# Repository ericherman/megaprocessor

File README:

http://www.megaprocessor.com/
(C) 2014-2016 James Newman.

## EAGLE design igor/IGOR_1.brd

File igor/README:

IGOR

This consists of an FPGA development board from Lattice piggybacking on
a board that provides 3 to 5V level translation to allow it to talk to
the Megaprocessor. I was originally only going to build one of these but
I ended up splitting out its functions (control, memory, peripherals) to
try and make it easier to see what was happening rather than just having
one board doing magic.
He's described in more detail here.
http://www.megaprocessor.com/igor.html

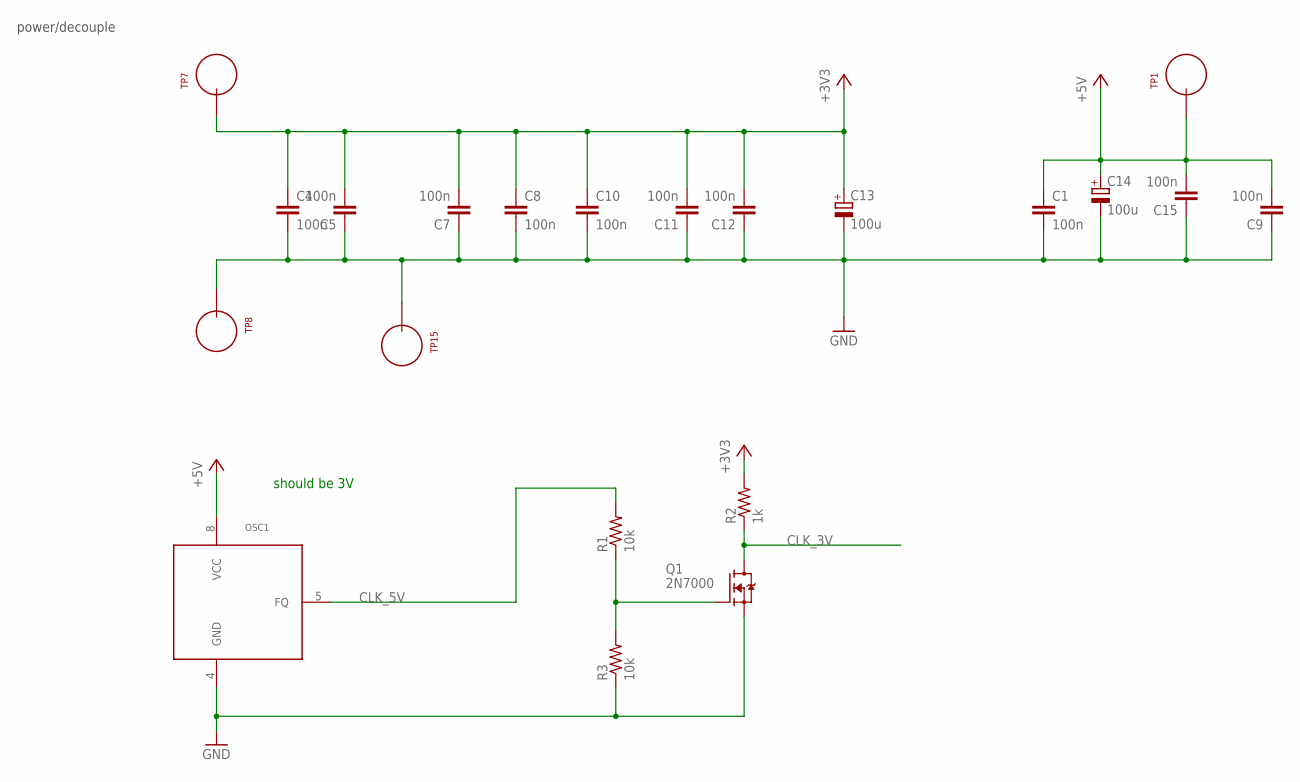
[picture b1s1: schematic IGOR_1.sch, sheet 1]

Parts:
C1, C4, C5, C7, C8, C9, C10, C11, C12, C15: 100n; CAP_P2INCH
C13, C14: 100u; POLARISED_CAP_2P5_6P3MM
OSC1: OSC_12P9_MM
Q1: 2N7000; TO92-DGS
R1, R3: 10k; R_P2INCH
R2: 1k; R_P2INCH
TP1, TP7, TP8, TP15: TEST_LOOP

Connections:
+3V3: C4.1, C5.2, C7.2, C8.1, C10.1, C11.2, C12.2, C13.A, R2.2, TP7.P$1; also elsewhere on the board
+5V: C1.1, C9.2, C14.A, C15.2, OSC1.8 (VCC), TP1.P$1; also elsewhere on the board
CLK_3V: Q1.D, R2.1; also elsewhere on the board
CLK_5V: Q1.G, R1.1, R3.2
GND: C1.2, C4.2, C5.1, C7.1, C8.2, C9.1, C10.2, C11.1, C12.1, C13.K, C14.K, C15.1, OSC1.4 (GND), Q1.S, R3.1, TP8.P$1, TP15.P$1; also elsewhere on the board
unnamed: OSC1.5 (FQ), R1.2

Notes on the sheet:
power/decouple
should be 3V

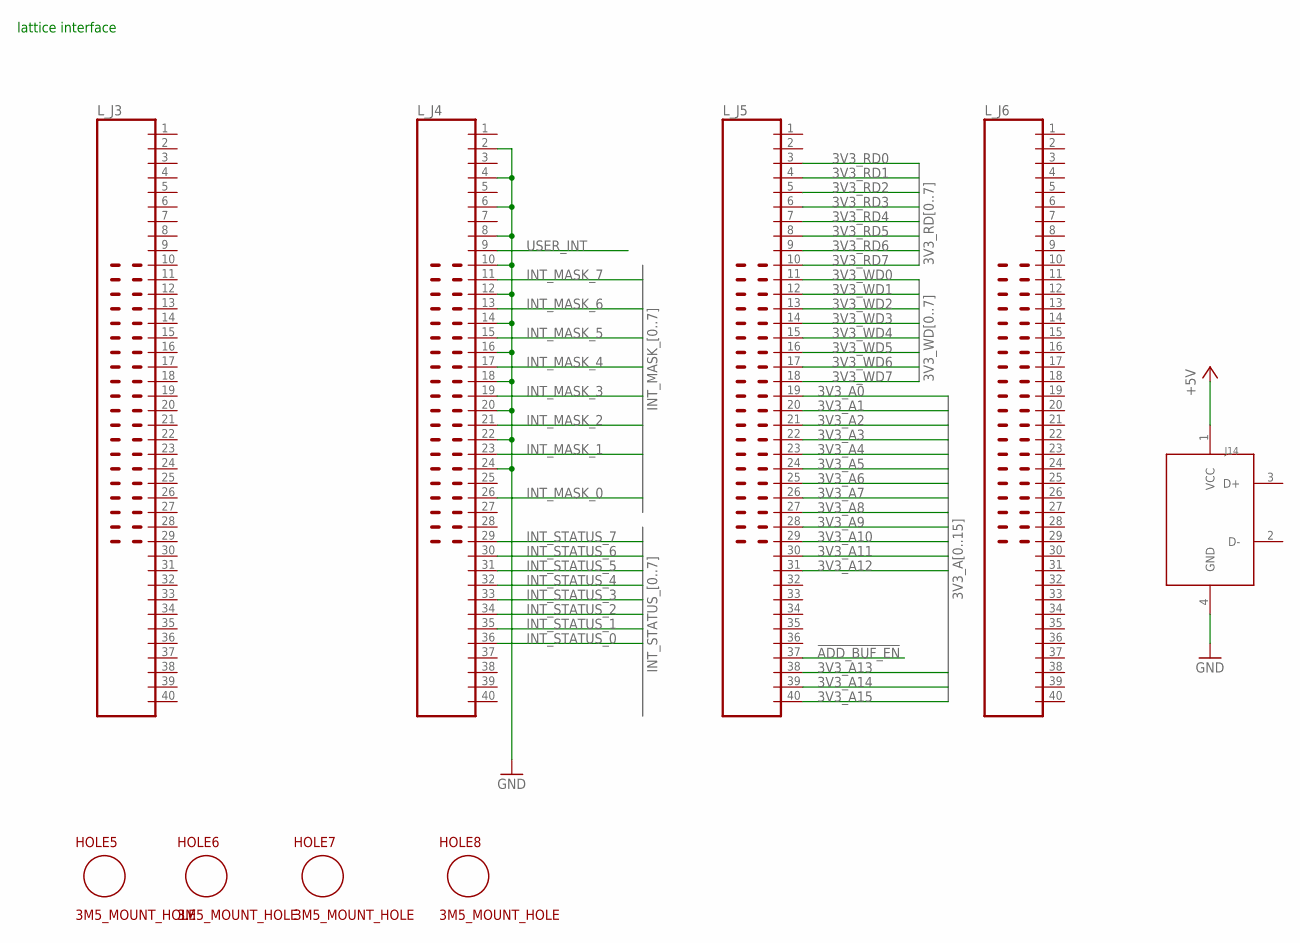
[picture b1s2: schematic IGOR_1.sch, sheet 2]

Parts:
HOLE5, HOLE6, HOLE7, HOLE8: 3M5_MOUNT_HOLE; 3P5M_HOLE
J14: USB_TYPE_A
L_J3, L_J4, L_J5, L_J6: JUMP_20X2

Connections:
3V3_A0: L_J5.19; also elsewhere on the board
3V3_A1: L_J5.20; also elsewhere on the board
3V3_A2: L_J5.21; also elsewhere on the board
3V3_A3: L_J5.22; also elsewhere on the board
3V3_A4: L_J5.23; also elsewhere on the board
3V3_A5: L_J5.24; also elsewhere on the board
3V3_A6: L_J5.25; also elsewhere on the board
3V3_A7: L_J5.26; also elsewhere on the board
3V3_A8: L_J5.27; also elsewhere on the board
3V3_A9: L_J5.28; also elsewhere on the board
3V3_A10: L_J5.29; also elsewhere on the board
3V3_A11: L_J5.30; also elsewhere on the board
3V3_A12: L_J5.31; also elsewhere on the board
3V3_A13: L_J5.38; also elsewhere on the board
3V3_A14: L_J5.39; also elsewhere on the board
3V3_A15: L_J5.40; also elsewhere on the board
3V3_RD0: L_J5.3; also elsewhere on the board
3V3_RD1: L_J5.4; also elsewhere on the board
3V3_RD2: L_J5.5; also elsewhere on the board
3V3_RD3: L_J5.6; also elsewhere on the board
3V3_RD4: L_J5.7; also elsewhere on the board
3V3_RD5: L_J5.8; also elsewhere on the board
3V3_RD6: L_J5.9; also elsewhere on the board
3V3_RD7: L_J5.10; also elsewhere on the board
3V3_WD0: L_J5.11; also elsewhere on the board
3V3_WD1: L_J5.12; also elsewhere on the board
3V3_WD2: L_J5.13; also elsewhere on the board
3V3_WD3: L_J5.14; also elsewhere on the board
3V3_WD4: L_J5.15; also elsewhere on the board
3V3_WD5: L_J5.16; also elsewhere on the board
3V3_WD6: L_J5.17; also elsewhere on the board
3V3_WD7: L_J5.18; also elsewhere on the board
!ADD_BUF_EN: L_J5.37; also elsewhere on the board
+5V: J14.1 (VCC); also elsewhere on the board
GND: J14.4 (GND), L_J4.2, L_J4.4, L_J4.6, L_J4.8, L_J4.10, L_J4.12, L_J4.14, L_J4.16, L_J4.18, L_J4.20, L_J4.22, L_J4.24; also elsewhere on the board
INT_MASK_0: L_J4.26; also elsewhere on the board
INT_MASK_1: L_J4.23; also elsewhere on the board
INT_MASK_2: L_J4.21; also elsewhere on the board
INT_MASK_3: L_J4.19; also elsewhere on the board
INT_MASK_4: L_J4.17; also elsewhere on the board
INT_MASK_5: L_J4.15; also elsewhere on the board
INT_MASK_6: L_J4.13; also elsewhere on the board
INT_MASK_7: L_J4.11; also elsewhere on the board
INT_STATUS_0: L_J4.36; also elsewhere on the board
INT_STATUS_1: L_J4.35; also elsewhere on the board
INT_STATUS_2: L_J4.34; also elsewhere on the board
INT_STATUS_3: L_J4.33; also elsewhere on the board
INT_STATUS_4: L_J4.32; also elsewhere on the board
INT_STATUS_5: L_J4.31; also elsewhere on the board
INT_STATUS_6: L_J4.30; also elsewhere on the board
INT_STATUS_7: L_J4.29; also elsewhere on the board
USER_INT: L_J4.9; also elsewhere on the board

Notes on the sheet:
lattice interface

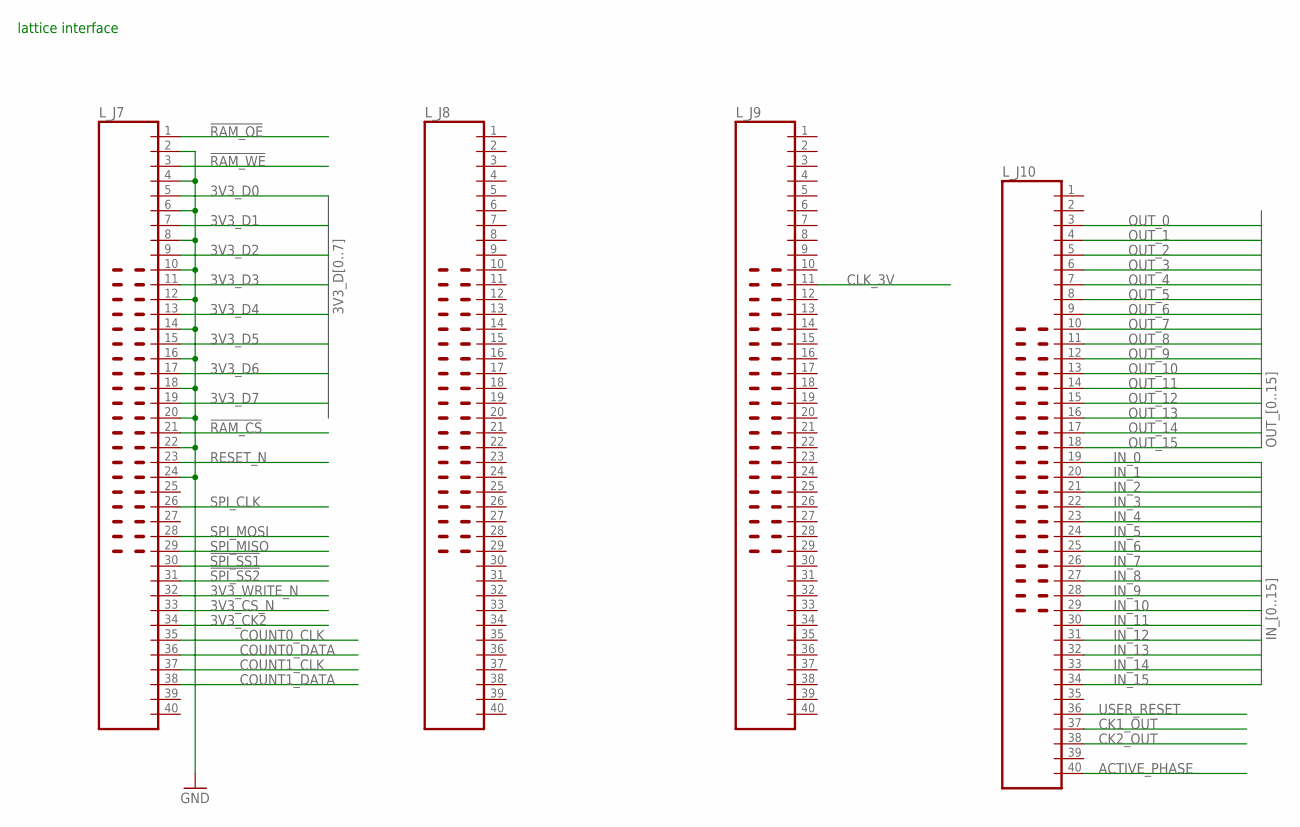
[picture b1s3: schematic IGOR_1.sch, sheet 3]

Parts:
L_J7, L_J8, L_J9, L_J10: JUMP_20X2

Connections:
3V3_CK2: L_J7.34; also elsewhere on the board
3V3_CS_N: L_J7.33; also elsewhere on the board
3V3_D0: L_J7.5; also elsewhere on the board
3V3_D1: L_J7.7; also elsewhere on the board
3V3_D2: L_J7.9; also elsewhere on the board
3V3_D3: L_J7.11; also elsewhere on the board
3V3_D4: L_J7.13; also elsewhere on the board
3V3_D5: L_J7.15; also elsewhere on the board
3V3_D6: L_J7.17; also elsewhere on the board
3V3_D7: L_J7.19; also elsewhere on the board
3V3_WRITE_N: L_J7.32; also elsewhere on the board
!RAM_CS: L_J7.21; also elsewhere on the board
!RAM_OE: L_J7.1; also elsewhere on the board
!RAM_WE: L_J7.3; also elsewhere on the board
!SPI_SS1: L_J7.30; also elsewhere on the board
!SPI_SS2: L_J7.31; also elsewhere on the board
ACTIVE_PHASE: L_J10.40; also elsewhere on the board
CK1_OUT: L_J10.37; also elsewhere on the board
CK2_OUT: L_J10.38; also elsewhere on the board
CLK_3V: L_J9.11; also elsewhere on the board
COUNT0_CLK: L_J7.35; also elsewhere on the board
COUNT0_DATA: L_J7.36; also elsewhere on the board
COUNT1_CLK: L_J7.37; also elsewhere on the board
COUNT1_DATA: L_J7.38; also elsewhere on the board
GND: L_J7.2, L_J7.4, L_J7.6, L_J7.8, L_J7.10, L_J7.12, L_J7.14, L_J7.16, L_J7.18, L_J7.20, L_J7.22, L_J7.24; also elsewhere on the board
IN_0: L_J10.19; also elsewhere on the board
IN_1: L_J10.20; also elsewhere on the board
IN_2: L_J10.21; also elsewhere on the board
IN_3: L_J10.22; also elsewhere on the board
IN_4: L_J10.23; also elsewhere on the board
IN_5: L_J10.24; also elsewhere on the board
IN_6: L_J10.25; also elsewhere on the board
IN_7: L_J10.26; also elsewhere on the board
IN_8: L_J10.27; also elsewhere on the board
IN_9: L_J10.28; also elsewhere on the board
IN_10: L_J10.29; also elsewhere on the board
IN_11: L_J10.30; also elsewhere on the board
IN_12: L_J10.31; also elsewhere on the board
IN_13: L_J10.32; also elsewhere on the board
IN_14: L_J10.33; also elsewhere on the board
IN_15: L_J10.34; also elsewhere on the board
OUT_0: L_J10.3; also elsewhere on the board
OUT_1: L_J10.4; also elsewhere on the board
OUT_2: L_J10.5; also elsewhere on the board
OUT_3: L_J10.6; also elsewhere on the board
OUT_4: L_J10.7; also elsewhere on the board
OUT_5: L_J10.8; also elsewhere on the board
OUT_6: L_J10.9; also elsewhere on the board
OUT_7: L_J10.10; also elsewhere on the board
OUT_8: L_J10.11; also elsewhere on the board
OUT_9: L_J10.12; also elsewhere on the board
OUT_10: L_J10.13; also elsewhere on the board
OUT_11: L_J10.14; also elsewhere on the board
OUT_12: L_J10.15; also elsewhere on the board
OUT_13: L_J10.16; also elsewhere on the board
OUT_14: L_J10.17; also elsewhere on the board
OUT_15: L_J10.18; also elsewhere on the board
RESET_N: L_J7.23; also elsewhere on the board
SPI_CLK: L_J7.26; also elsewhere on the board
SPI_MISO: L_J7.29; also elsewhere on the board
SPI_MOSI: L_J7.28; also elsewhere on the board
USER_RESET: L_J10.36; also elsewhere on the board

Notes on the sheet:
lattice interface

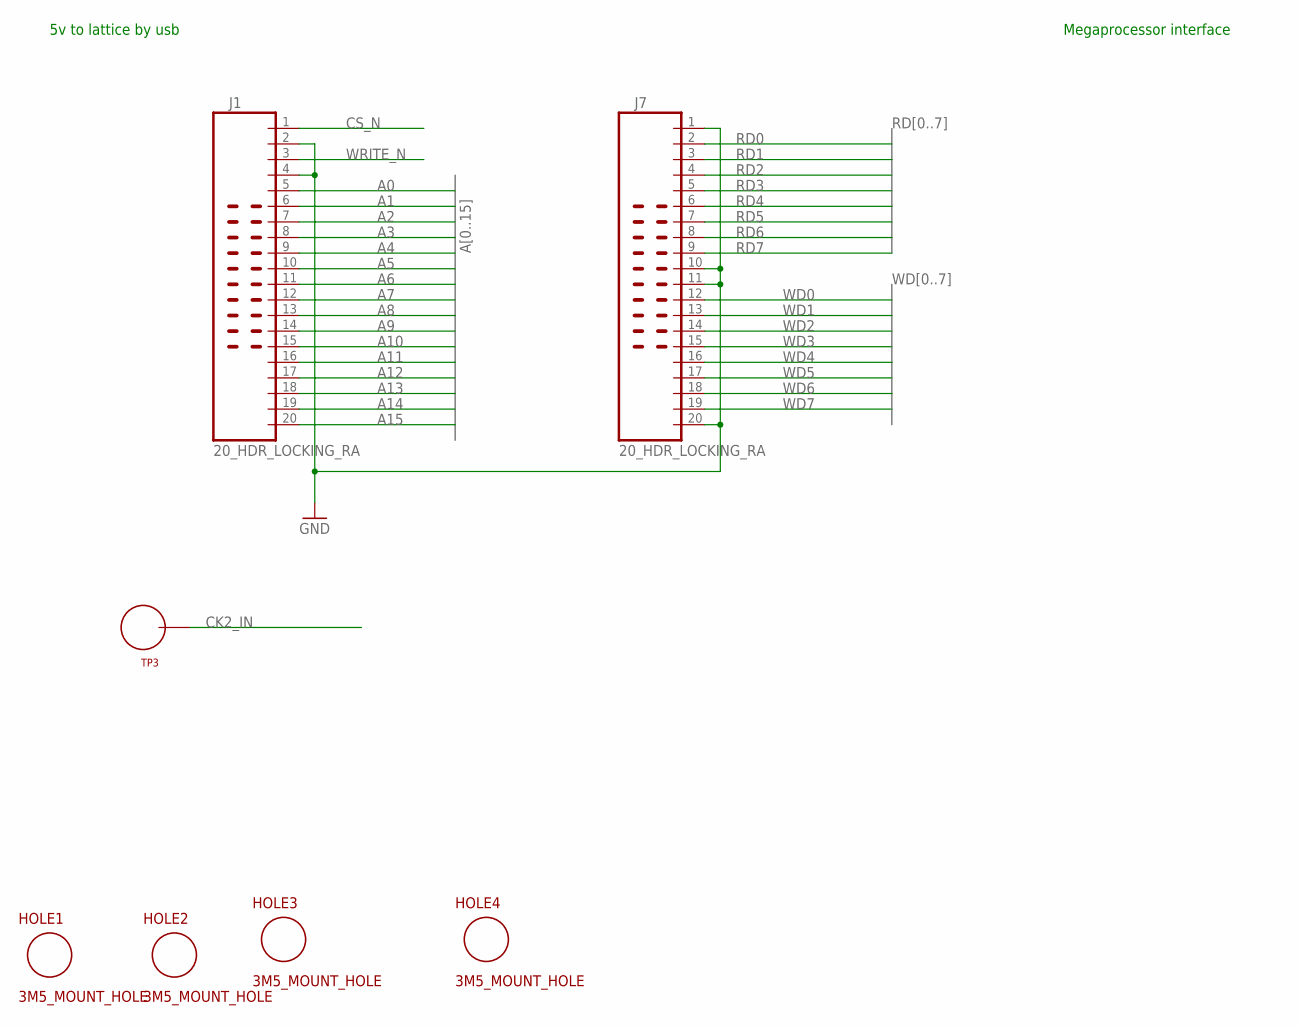
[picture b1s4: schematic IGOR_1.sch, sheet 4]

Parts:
HOLE1, HOLE2, HOLE3, HOLE4: 3M5_MOUNT_HOLE; 3P5M_HOLE
J1, J7: 20_HDR_LOCKING_RA
TP3: TEST_LOOP

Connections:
A0: J1.5; also elsewhere on the board
A1: J1.6; also elsewhere on the board
A2: J1.7; also elsewhere on the board
A3: J1.8; also elsewhere on the board
A4: J1.9; also elsewhere on the board
A5: J1.10; also elsewhere on the board
A6: J1.11; also elsewhere on the board
A7: J1.12; also elsewhere on the board
A8: J1.13; also elsewhere on the board
A9: J1.14; also elsewhere on the board
A10: J1.15; also elsewhere on the board
A11: J1.16; also elsewhere on the board
A12: J1.17; also elsewhere on the board
A13: J1.18; also elsewhere on the board
A14: J1.19; also elsewhere on the board
A15: J1.20; also elsewhere on the board
CK2_IN: TP3.P$1; also elsewhere on the board
CS_N: J1.1; also elsewhere on the board
GND: J1.2, J1.4, J7.1, J7.10, J7.11, J7.20; also elsewhere on the board
RD0: J7.2; also elsewhere on the board
RD1: J7.3; also elsewhere on the board
RD2: J7.4; also elsewhere on the board
RD3: J7.5; also elsewhere on the board
RD4: J7.6; also elsewhere on the board
RD5: J7.7; also elsewhere on the board
RD6: J7.8; also elsewhere on the board
RD7: J7.9; also elsewhere on the board
WD0: J7.12; also elsewhere on the board
WD1: J7.13; also elsewhere on the board
WD2: J7.14; also elsewhere on the board
WD3: J7.15; also elsewhere on the board
WD4: J7.16; also elsewhere on the board
WD5: J7.17; also elsewhere on the board
WD6: J7.18; also elsewhere on the board
WD7: J7.19; also elsewhere on the board
WRITE_N: J1.3; also elsewhere on the board

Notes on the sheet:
5v to lattice by usb
Megaprocessor interface

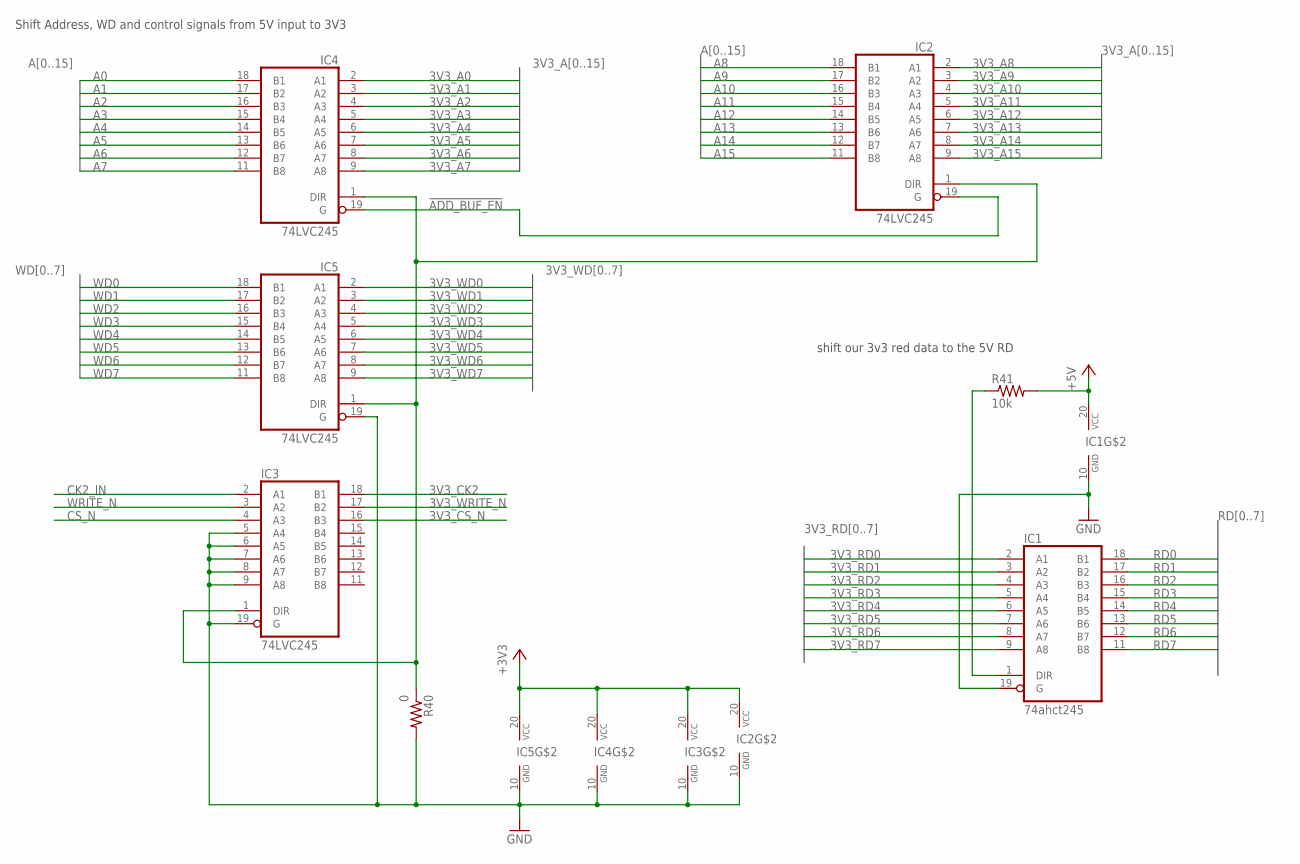
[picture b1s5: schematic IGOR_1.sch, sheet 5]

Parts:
IC1: 74ahct245; DIP20
IC2, IC3, IC4, IC5: 74LVC245; DIP20
R40: 0; R_P2INCH
R41: 10k; R_P2INCH

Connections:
3V3_A0: IC4.2 (A1); also elsewhere on the board
3V3_A1: IC4.3 (A2); also elsewhere on the board
3V3_A2: IC4.4 (A3); also elsewhere on the board
3V3_A3: IC4.5 (A4); also elsewhere on the board
3V3_A4: IC4.6 (A5); also elsewhere on the board
3V3_A5: IC4.7 (A6); also elsewhere on the board
3V3_A6: IC4.8 (A7); also elsewhere on the board
3V3_A7: IC4.9 (A8); also elsewhere on the board
3V3_A8: IC2.2 (A1); also elsewhere on the board
3V3_A9: IC2.3 (A2); also elsewhere on the board
3V3_A10: IC2.4 (A3); also elsewhere on the board
3V3_A11: IC2.5 (A4); also elsewhere on the board
3V3_A12: IC2.6 (A5); also elsewhere on the board
3V3_A13: IC2.7 (A6); also elsewhere on the board
3V3_A14: IC2.8 (A7); also elsewhere on the board
3V3_A15: IC2.9 (A8); also elsewhere on the board
3V3_CK2: IC3.18 (B1); also elsewhere on the board
3V3_CS_N: IC3.16 (B3); also elsewhere on the board
3V3_RD0: IC1.2 (A1); also elsewhere on the board
3V3_RD1: IC1.3 (A2); also elsewhere on the board
3V3_RD2: IC1.4 (A3); also elsewhere on the board
3V3_RD3: IC1.5 (A4); also elsewhere on the board
3V3_RD4: IC1.6 (A5); also elsewhere on the board
3V3_RD5: IC1.7 (A6); also elsewhere on the board
3V3_RD6: IC1.8 (A7); also elsewhere on the board
3V3_RD7: IC1.9 (A8); also elsewhere on the board
3V3_WD0: IC5.2 (A1); also elsewhere on the board
3V3_WD1: IC5.3 (A2); also elsewhere on the board
3V3_WD2: IC5.4 (A3); also elsewhere on the board
3V3_WD3: IC5.5 (A4); also elsewhere on the board
3V3_WD4: IC5.6 (A5); also elsewhere on the board
3V3_WD5: IC5.7 (A6); also elsewhere on the board
3V3_WD6: IC5.8 (A7); also elsewhere on the board
3V3_WD7: IC5.9 (A8); also elsewhere on the board
3V3_WRITE_N: IC3.17 (B2); also elsewhere on the board
!ADD_BUF_EN: IC2.19 (G), IC4.19 (G); also elsewhere on the board
+3V3: IC2.20 (VCC), IC3.20 (VCC), IC4.20 (VCC), IC5.20 (VCC); also elsewhere on the board
+5V: IC1.20 (VCC), R41.2; also elsewhere on the board
A0: IC4.18 (B1); also elsewhere on the board
A1: IC4.17 (B2); also elsewhere on the board
A2: IC4.16 (B3); also elsewhere on the board
A3: IC4.15 (B4); also elsewhere on the board
A4: IC4.14 (B5); also elsewhere on the board
A5: IC4.13 (B6); also elsewhere on the board
A6: IC4.12 (B7); also elsewhere on the board
A7: IC4.11 (B8); also elsewhere on the board
A8: IC2.18 (B1); also elsewhere on the board
A9: IC2.17 (B2); also elsewhere on the board
A10: IC2.16 (B3); also elsewhere on the board
A11: IC2.15 (B4); also elsewhere on the board
A12: IC2.14 (B5); also elsewhere on the board
A13: IC2.13 (B6); also elsewhere on the board
A14: IC2.12 (B7); also elsewhere on the board
A15: IC2.11 (B8); also elsewhere on the board
CK2_IN: IC3.2 (A1); also elsewhere on the board
CS_N: IC3.4 (A3); also elsewhere on the board
GND: IC1.10 (GND), IC1.19 (G), IC2.10 (GND), IC3.5 (A4), IC3.6 (A5), IC3.7 (A6), IC3.8 (A7), IC3.9 (A8), IC3.10 (GND), IC3.19 (G), IC4.10 (GND), IC5.10 (GND), IC5.19 (G), R40.2; also elsewhere on the board
unnamed: IC2.1 (DIR), IC3.1 (DIR), IC4.1 (DIR), IC5.1 (DIR), R40.1
unnamed: IC1.1 (DIR), R41.1
RD0: IC1.18 (B1); also elsewhere on the board
RD1: IC1.17 (B2); also elsewhere on the board
RD2: IC1.16 (B3); also elsewhere on the board
RD3: IC1.15 (B4); also elsewhere on the board
RD4: IC1.14 (B5); also elsewhere on the board
RD5: IC1.13 (B6); also elsewhere on the board
RD6: IC1.12 (B7); also elsewhere on the board
RD7: IC1.11 (B8); also elsewhere on the board
WD0: IC5.18 (B1); also elsewhere on the board
WD1: IC5.17 (B2); also elsewhere on the board
WD2: IC5.16 (B3); also elsewhere on the board
WD3: IC5.15 (B4); also elsewhere on the board
WD4: IC5.14 (B5); also elsewhere on the board
WD5: IC5.13 (B6); also elsewhere on the board
WD6: IC5.12 (B7); also elsewhere on the board
WD7: IC5.11 (B8); also elsewhere on the board
WRITE_N: IC3.3 (A2); also elsewhere on the board

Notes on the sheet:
Shift Address, WD and control signals from 5V input to 3V3
shift our 3v3 red data to the 5V RD

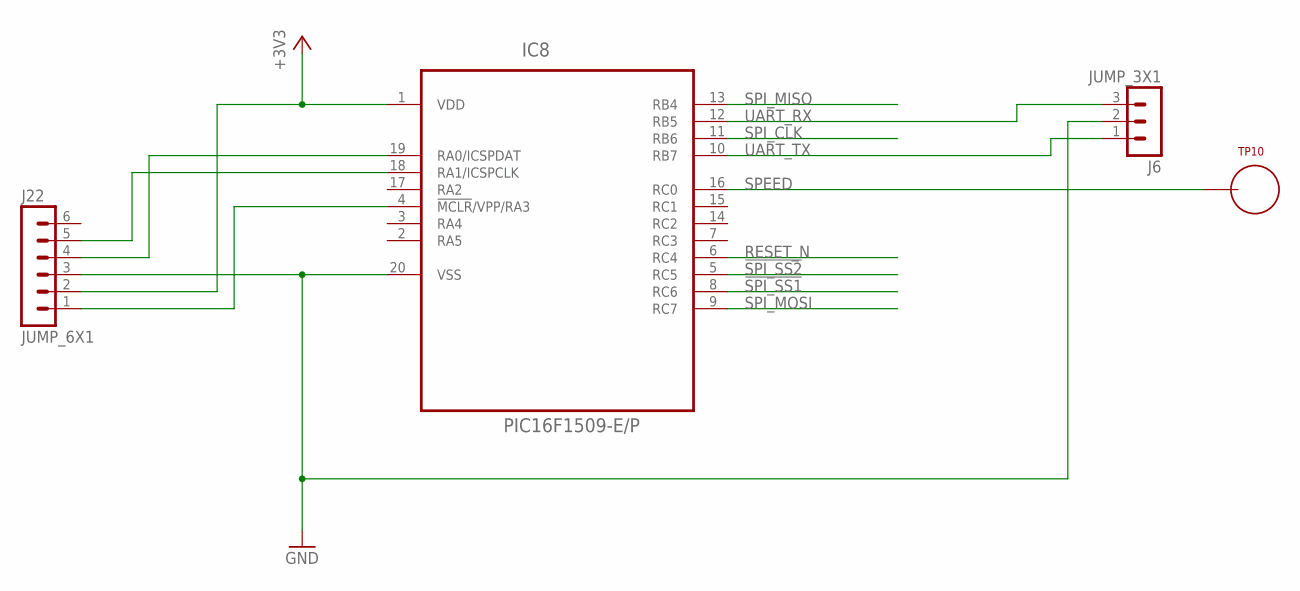
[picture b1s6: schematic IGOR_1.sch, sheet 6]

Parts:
IC8: PIC16F1509-E/P; DIP20
J6: JUMP_3X1
J22: JUMP_6X1
TP10: TEST_LOOP

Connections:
!SPI_SS1: IC8.8 (RC6); also elsewhere on the board
!SPI_SS2: IC8.5 (RC5); also elsewhere on the board
+3V3: IC8.1 (VDD), J22.2; also elsewhere on the board
GND: IC8.20 (VSS), J6.2, J22.3; also elsewhere on the board
unnamed: IC8.19 (RA0/ICSPDAT), J22.4
unnamed: IC8.18 (RA1/ICSPCLK), J22.5
unnamed: IC8.4 (!MCLR!/VPP/RA3), J22.1
RESET_N: IC8.6 (RC4); also elsewhere on the board
SPEED: IC8.16 (RC0), TP10.P$1
SPI_CLK: IC8.11 (RB6); also elsewhere on the board
SPI_MISO: IC8.13 (RB4); also elsewhere on the board
SPI_MOSI: IC8.9 (RC7); also elsewhere on the board
UART_RX: IC8.12 (RB5), J6.3
UART_TX: IC8.10 (RB7), J6.1

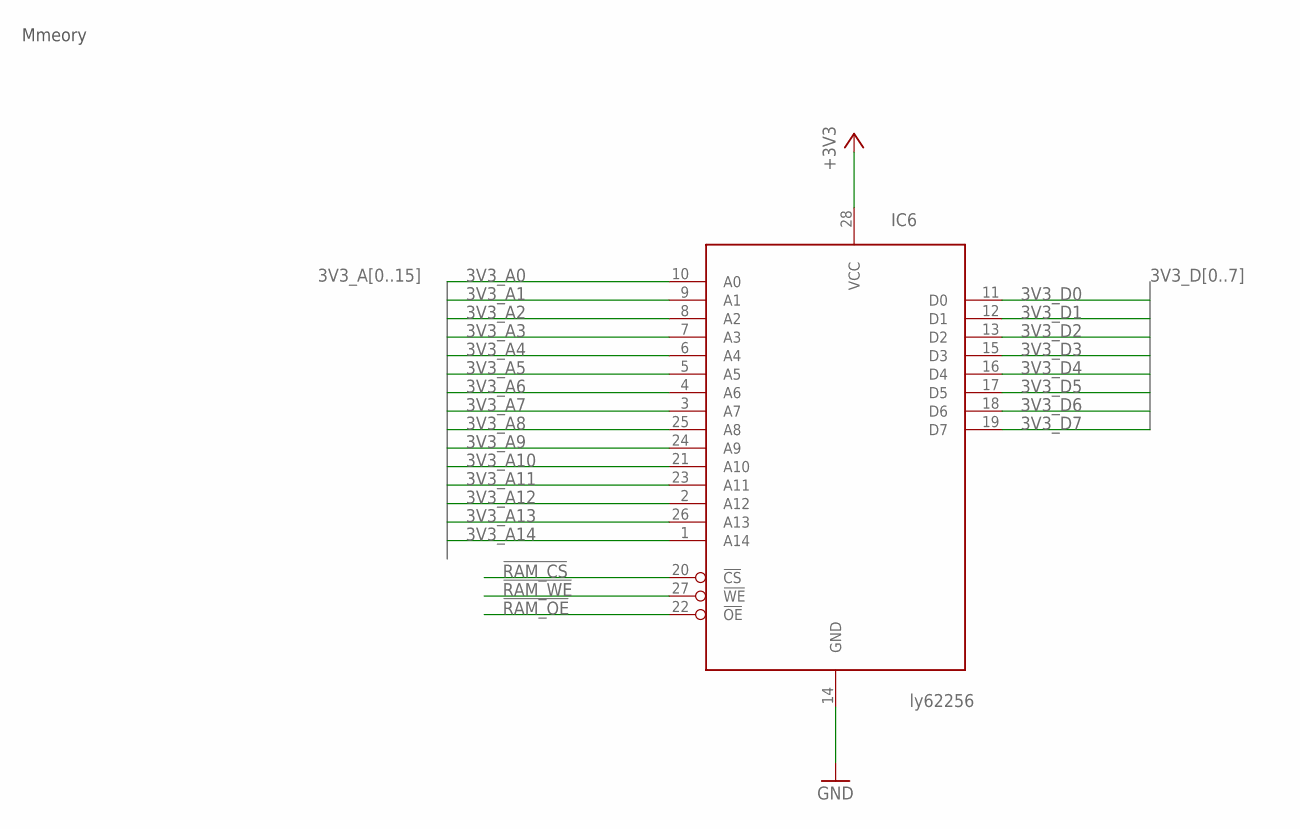
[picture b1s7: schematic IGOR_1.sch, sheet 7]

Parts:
IC6: ly62256; DIP28

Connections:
3V3_A0: IC6.10 (A0); also elsewhere on the board
3V3_A1: IC6.9 (A1); also elsewhere on the board
3V3_A2: IC6.8 (A2); also elsewhere on the board
3V3_A3: IC6.7 (A3); also elsewhere on the board
3V3_A4: IC6.6 (A4); also elsewhere on the board
3V3_A5: IC6.5 (A5); also elsewhere on the board
3V3_A6: IC6.4 (A6); also elsewhere on the board
3V3_A7: IC6.3 (A7); also elsewhere on the board
3V3_A8: IC6.25 (A8); also elsewhere on the board
3V3_A9: IC6.24 (A9); also elsewhere on the board
3V3_A10: IC6.21 (A10); also elsewhere on the board
3V3_A11: IC6.23 (A11); also elsewhere on the board
3V3_A12: IC6.2 (A12); also elsewhere on the board
3V3_A13: IC6.26 (A13); also elsewhere on the board
3V3_A14: IC6.1 (A14); also elsewhere on the board
3V3_D0: IC6.11 (D0); also elsewhere on the board
3V3_D1: IC6.12 (D1); also elsewhere on the board
3V3_D2: IC6.13 (D2); also elsewhere on the board
3V3_D3: IC6.15 (D3); also elsewhere on the board
3V3_D4: IC6.16 (D4); also elsewhere on the board
3V3_D5: IC6.17 (D5); also elsewhere on the board
3V3_D6: IC6.18 (D6); also elsewhere on the board
3V3_D7: IC6.19 (D7); also elsewhere on the board
!RAM_CS: IC6.20 (!CS); also elsewhere on the board
!RAM_OE: IC6.22 (!OE); also elsewhere on the board
!RAM_WE: IC6.27 (!WE); also elsewhere on the board
+3V3: IC6.28 (VCC); also elsewhere on the board
GND: IC6.14 (GND); also elsewhere on the board

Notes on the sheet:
Mmeory

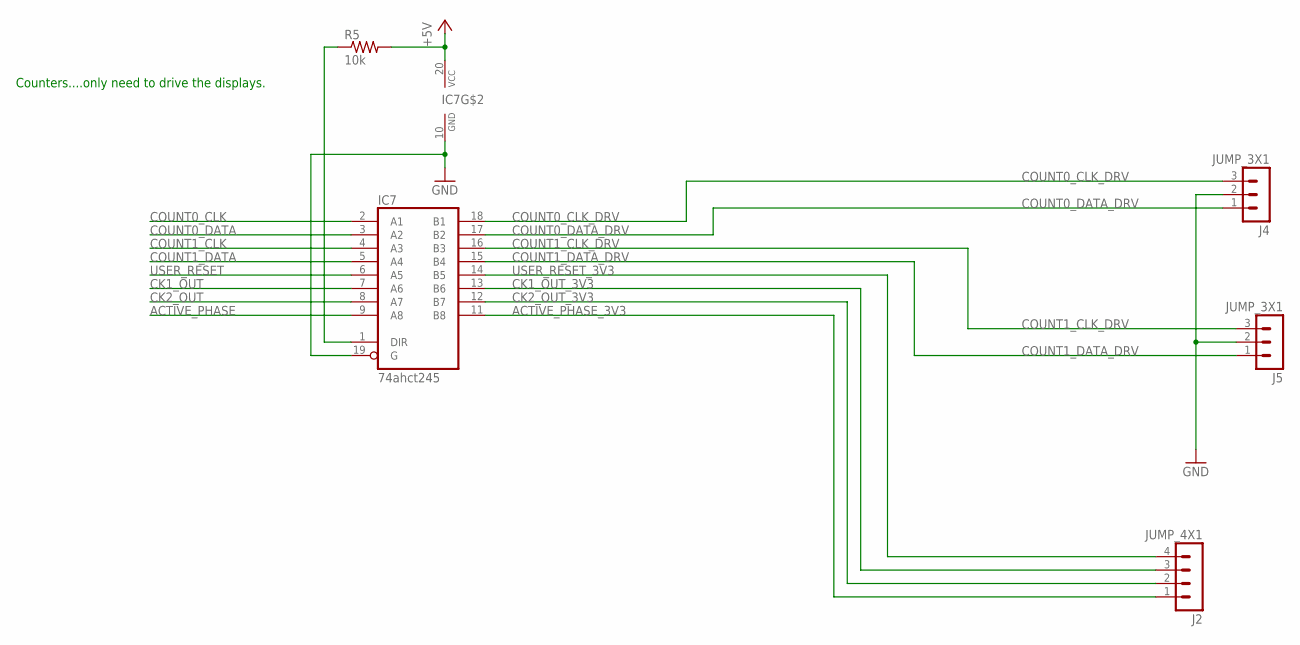
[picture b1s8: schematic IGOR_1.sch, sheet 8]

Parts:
IC7: 74ahct245; DIP20
J2: JUMP_4X1
J4, J5: JUMP_3X1
R5: 10k; R_P2INCH

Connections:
+5V: IC7.20 (VCC), R5.2; also elsewhere on the board
ACTIVE_PHASE: IC7.9 (A8); also elsewhere on the board
ACTIVE_PHASE_3V3: IC7.11 (B8), J2.1
CK1_OUT: IC7.7 (A6); also elsewhere on the board
CK1_OUT_3V3: IC7.13 (B6), J2.3
CK2_OUT: IC7.8 (A7); also elsewhere on the board
CK2_OUT_3V3: IC7.12 (B7), J2.2
COUNT0_CLK: IC7.2 (A1); also elsewhere on the board
COUNT0_CLK_DRV: IC7.18 (B1), J4.3
COUNT0_DATA: IC7.3 (A2); also elsewhere on the board
COUNT0_DATA_DRV: IC7.17 (B2), J4.1
COUNT1_CLK: IC7.4 (A3); also elsewhere on the board
COUNT1_CLK_DRV: IC7.16 (B3), J5.3
COUNT1_DATA: IC7.5 (A4); also elsewhere on the board
COUNT1_DATA_DRV: IC7.15 (B4), J5.1
GND: IC7.10 (GND), IC7.19 (G), J4.2, J5.2; also elsewhere on the board
unnamed: IC7.1 (DIR), R5.1
USER_RESET: IC7.6 (A5); also elsewhere on the board
USER_RESET_3V3: IC7.14 (B5), J2.4

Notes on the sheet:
Counters....only need to drive the displays.

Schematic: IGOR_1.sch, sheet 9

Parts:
J9: 20_HDR_LOCKING_RA
R51, R52, R53, R54, R55, R56, R57, R58, R59, R60, R61, R62, R63, R64, R65, R66: 10k; R_P2INCH
TP11, TP12, TP13, TP14: TEST_LOOP

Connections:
+3V3: R51.1, R52.1, R53.1, R54.1, R55.1, R56.1, R57.1, R58.1, R59.1, R60.1, R61.1, R62.1, R63.1, R64.1, R65.1, R66.1; also elsewhere on the board
GND: J9.1, J9.10, J9.11, J9.20; also elsewhere on the board
IN_0: J9.2, R66.2, TP11.P$1; also elsewhere on the board
IN_1: J9.3, R65.2, TP12.P$1; also elsewhere on the board
IN_2: J9.4, R64.2, TP13.P$1; also elsewhere on the board
IN_3: J9.5, R63.2, TP14.P$1; also elsewhere on the board
IN_4: J9.6, R62.2; also elsewhere on the board
IN_5: J9.7, R61.2; also elsewhere on the board
IN_6: J9.8, R60.2; also elsewhere on the board
IN_7: J9.9, R59.2; also elsewhere on the board
IN_8: J9.12, R58.2; also elsewhere on the board
IN_9: J9.13, R57.2; also elsewhere on the board
IN_10: J9.14, R56.2; also elsewhere on the board
IN_11: J9.15, R55.2; also elsewhere on the board
IN_12: J9.16, R54.2; also elsewhere on the board
IN_13: J9.17, R53.2; also elsewhere on the board
IN_14: J9.18, R52.2; also elsewhere on the board
IN_15: J9.19, R51.2; also elsewhere on the board

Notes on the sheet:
I/O : Input

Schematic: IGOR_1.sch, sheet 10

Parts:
J11: 20_HDR_LOCKING_RA
TP4, TP5, TP6, TP9: TEST_LOOP

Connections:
GND: J11.1, J11.10, J11.11, J11.20; also elsewhere on the board
OUT_0: J11.2, TP4.P$1; also elsewhere on the board
OUT_1: J11.3, TP5.P$1; also elsewhere on the board
OUT_2: J11.4, TP6.P$1; also elsewhere on the board
OUT_3: J11.5, TP9.P$1; also elsewhere on the board
OUT_4: J11.6; also elsewhere on the board
OUT_5: J11.7; also elsewhere on the board
OUT_6: J11.8; also elsewhere on the board
OUT_7: J11.9; also elsewhere on the board
OUT_8: J11.12; also elsewhere on the board
OUT_9: J11.13; also elsewhere on the board
OUT_10: J11.14; also elsewhere on the board
OUT_11: J11.15; also elsewhere on the board
OUT_12: J11.16; also elsewhere on the board
OUT_13: J11.17; also elsewhere on the board
OUT_14: J11.18; also elsewhere on the board
OUT_15: J11.19; also elsewhere on the board

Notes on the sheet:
I/O : output

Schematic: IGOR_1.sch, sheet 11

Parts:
J3: 20_HDR_LOCKING_RA
R39: 10k; R_P2INCH
TP2: TEST_LOOP

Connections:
+3V3: R39.2; also elsewhere on the board
GND: J3.1, J3.10, J3.11, J3.12, J3.13, J3.14, J3.15, J3.16, J3.17, J3.18, J3.19, J3.20; also elsewhere on the board
INT_STATUS_0: J3.2; also elsewhere on the board
INT_STATUS_1: J3.3; also elsewhere on the board
INT_STATUS_2: J3.4; also elsewhere on the board
INT_STATUS_3: J3.5; also elsewhere on the board
INT_STATUS_4: J3.6; also elsewhere on the board
INT_STATUS_5: J3.7; also elsewhere on the board
INT_STATUS_6: J3.8; also elsewhere on the board
INT_STATUS_7: J3.9; also elsewhere on the board
USER_INT: R39.1, TP2.P$1; also elsewhere on the board

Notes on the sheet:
Interrupts - status

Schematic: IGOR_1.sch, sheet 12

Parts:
J12: 20_HDR_LOCKING_RA

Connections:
GND: J12.1, J12.10, J12.11, J12.12, J12.13, J12.14, J12.15, J12.16, J12.17, J12.18, J12.19, J12.20; also elsewhere on the board
INT_MASK_0: J12.2; also elsewhere on the board
INT_MASK_1: J12.3; also elsewhere on the board
INT_MASK_2: J12.4; also elsewhere on the board
INT_MASK_3: J12.5; also elsewhere on the board
INT_MASK_4: J12.6; also elsewhere on the board
INT_MASK_5: J12.7; also elsewhere on the board
INT_MASK_6: J12.8; also elsewhere on the board
INT_MASK_7: J12.9; also elsewhere on the board

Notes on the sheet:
Interrupts : Masks
mask_drv

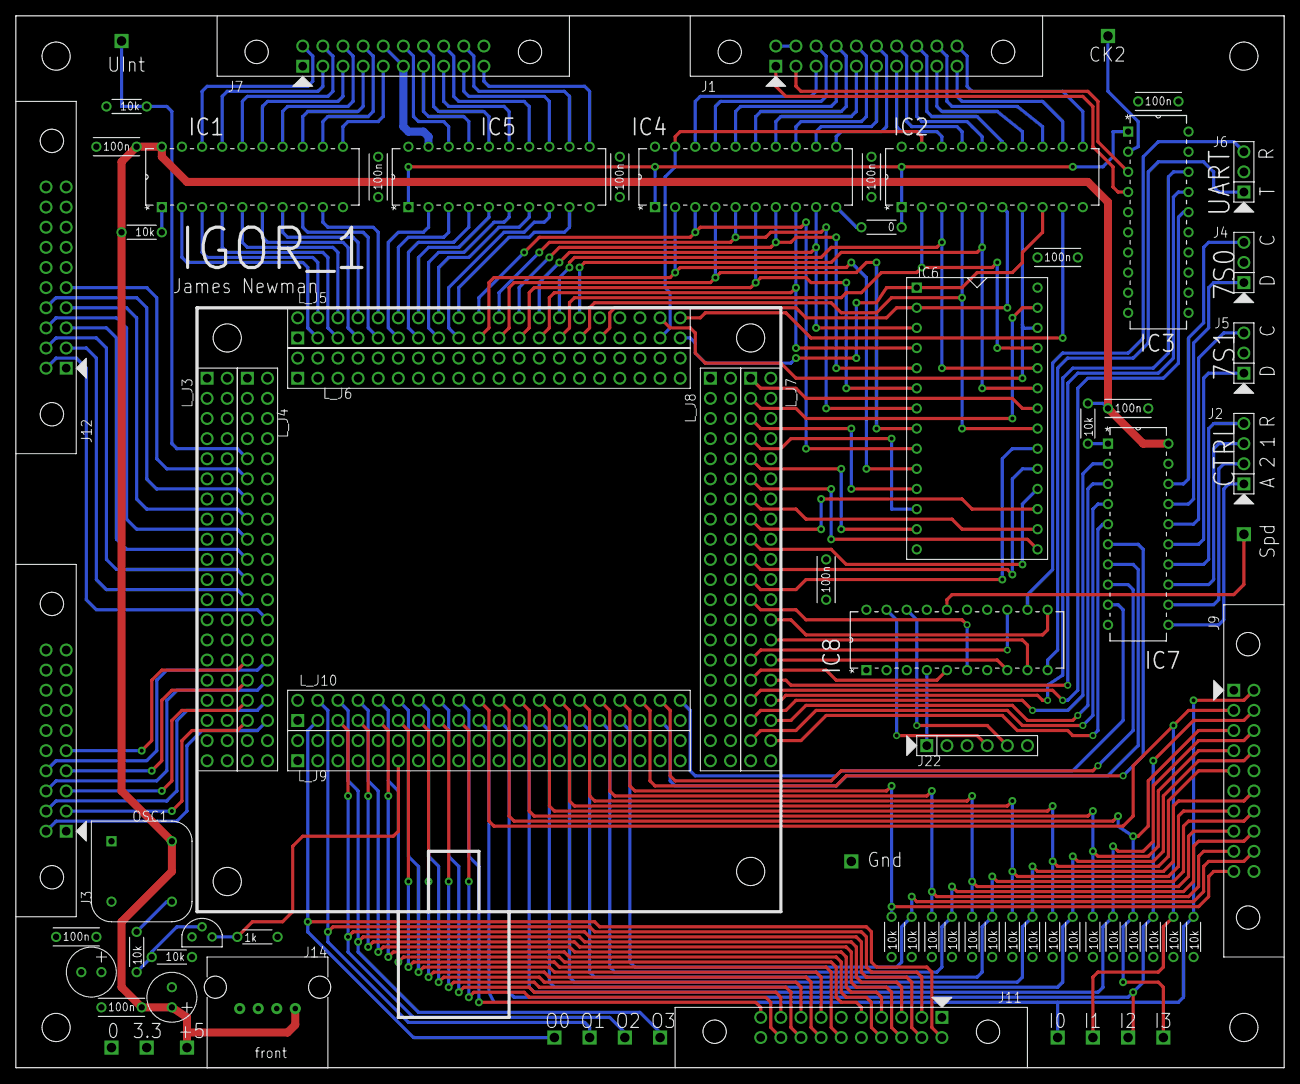
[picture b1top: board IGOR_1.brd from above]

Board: 4 copper layers, 160.0 x 132.7 mm, 88 parts (0 on the bottom side), 168 nets.

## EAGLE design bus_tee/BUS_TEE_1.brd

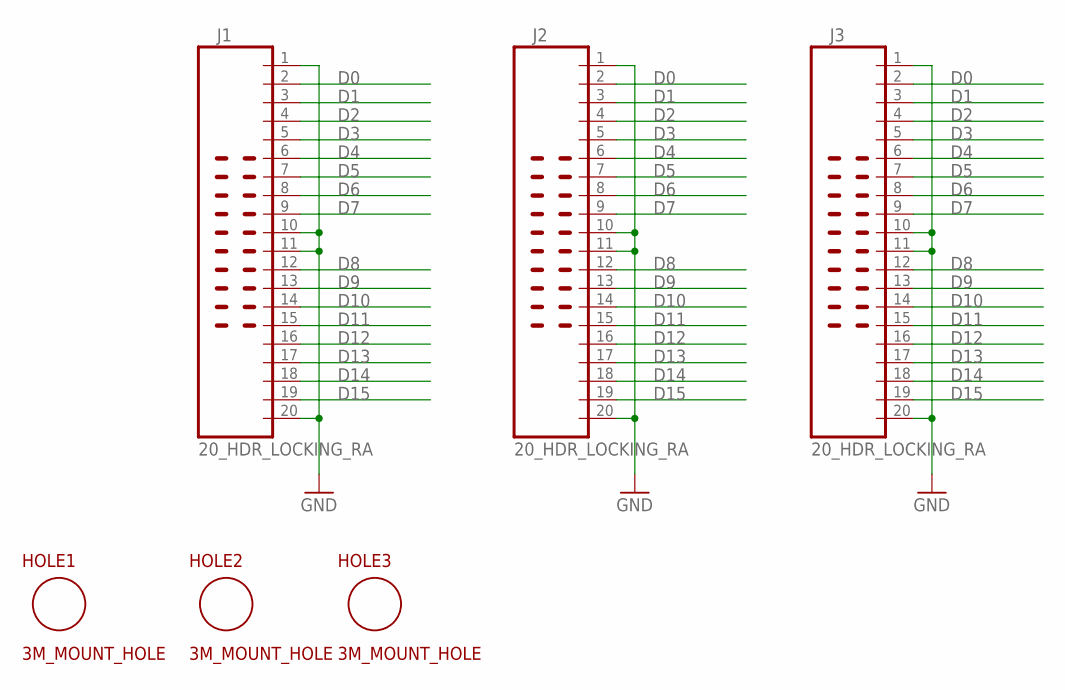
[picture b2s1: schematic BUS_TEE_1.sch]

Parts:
HOLE1, HOLE2, HOLE3: 3M_MOUNT_HOLE; 3M_HOLE
J1, J2, J3: 20_HDR_LOCKING_RA

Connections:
D0: J1.2, J2.2, J3.2
D1: J1.3, J2.3, J3.3
D2: J1.4, J2.4, J3.4
D3: J1.5, J2.5, J3.5
D4: J1.6, J2.6, J3.6
D5: J1.7, J2.7, J3.7
D6: J1.8, J2.8, J3.8
D7: J1.9, J2.9, J3.9
D8: J1.12, J2.12, J3.12
D9: J1.13, J2.13, J3.13
D10: J1.14, J2.14, J3.14
D11: J1.15, J2.15, J3.15
D12: J1.16, J2.16, J3.16
D13: J1.17, J2.17, J3.17
D14: J1.18, J2.18, J3.18
D15: J1.19, J2.19, J3.19
GND: J1.1, J1.10, J1.11, J1.20, J2.1, J2.10, J2.11, J2.20, J3.1, J3.10, J3.11, J3.20
